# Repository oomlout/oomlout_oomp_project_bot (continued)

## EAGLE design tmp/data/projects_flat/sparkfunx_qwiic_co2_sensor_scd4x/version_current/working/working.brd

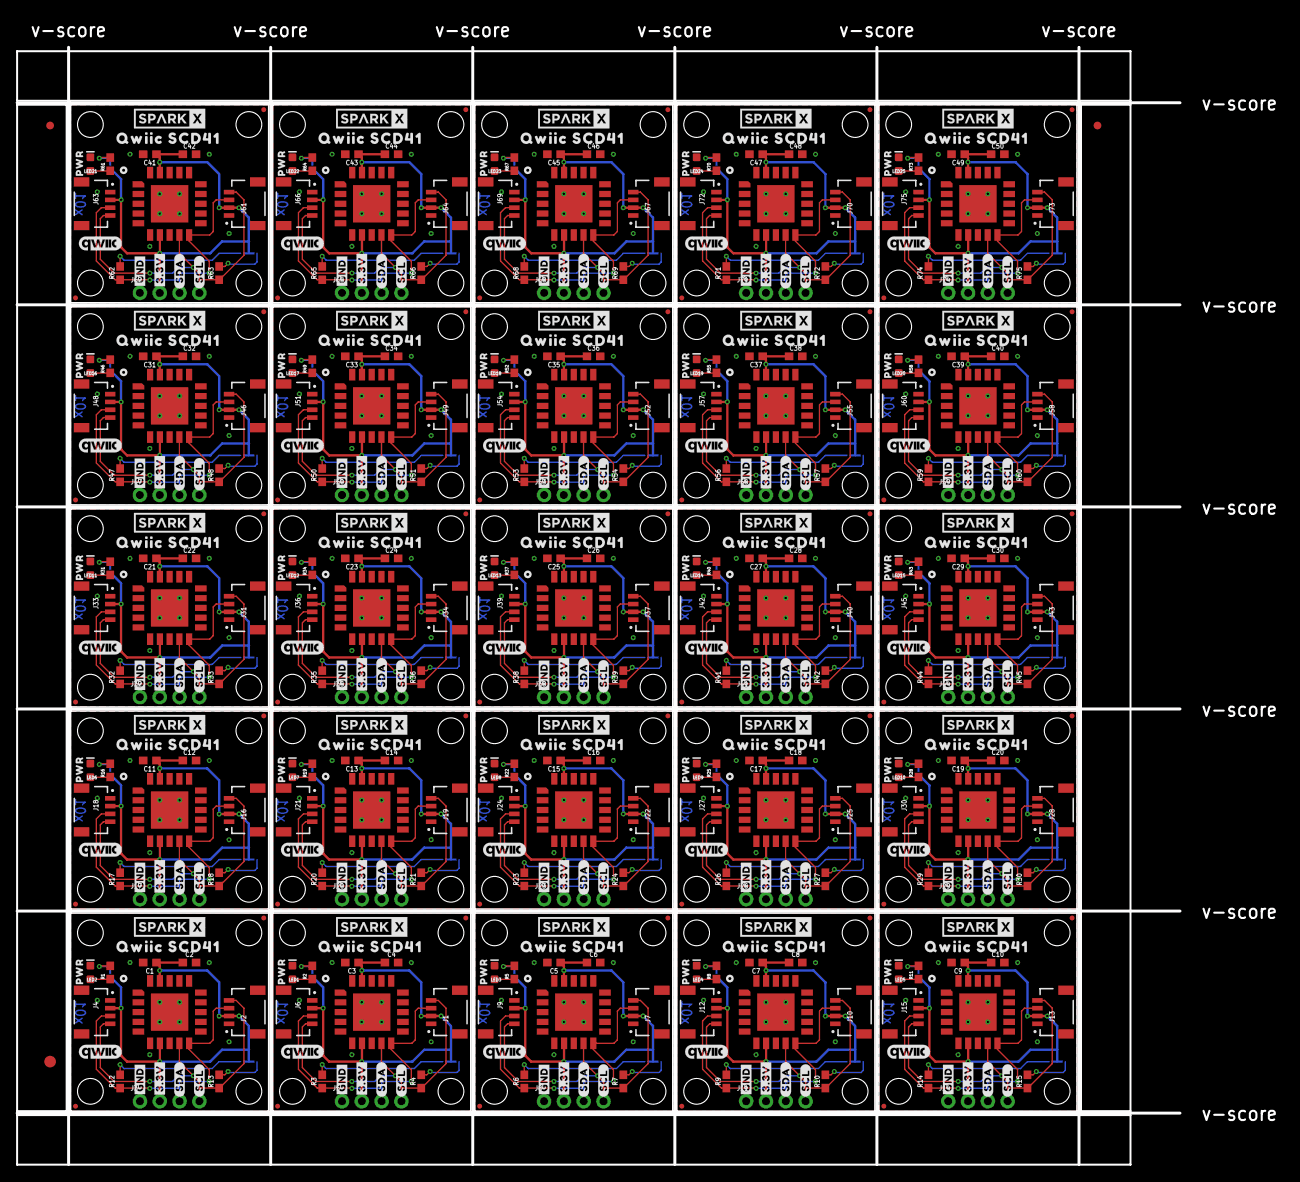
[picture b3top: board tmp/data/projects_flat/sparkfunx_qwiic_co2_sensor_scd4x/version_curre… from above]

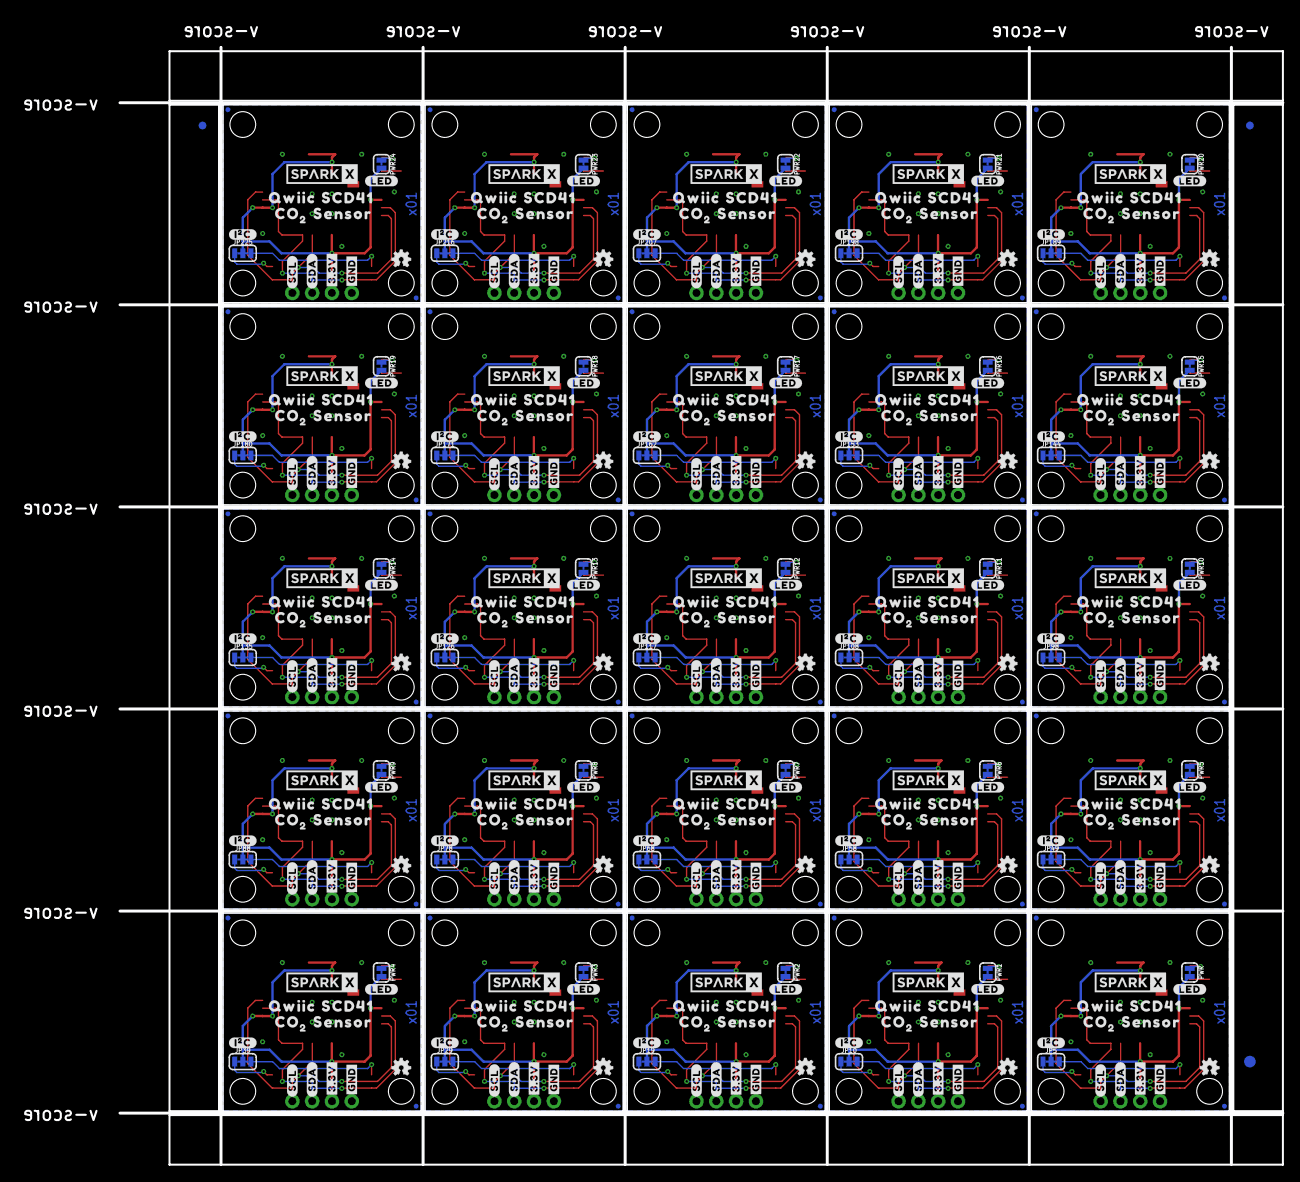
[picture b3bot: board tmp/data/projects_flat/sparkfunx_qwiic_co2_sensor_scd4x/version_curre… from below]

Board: 2 copper layers, 149.1 x 143.3 mm, 1056 parts (428 on the bottom side), 200 nets.

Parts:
C1, C3, C5, C7, C9, C11, C13, C15, C17, C19, C21, C23, C25, C27, C29, C31, C33, C35, C37, C39, C41, C43, C45, C47, C49: 0.1uF; 0603
C2, C4, C6, C8, C10, C12, C14, C16, C18, C20, C22, C24, C26, C28, C30, C32, C34, C36, C38, C40, C42, C44, C46, C48, C50: 4.7uF; 0603
E$1, E$2, E$3, E$4: FIDUCIAL-1X2
E$5, E$6: FIDUCIAL-1.5X3
J1, J2, J4, J6, J7, J9, J10, J12, J13, J15, J16, J18, J19, J21, J22, J24, J25, J27, J28, J30, J31, J33, J34, J36, J37, J39, J40, J42, J43, J45, J46, J48, J49, J51, J52, J54, J55, J57, J58, J60, J61, J63, J64, J66, J67, J69, J70, J72, J73, J75: Qwiic Right Angle; JST04_1MM_RA
J3, J5, J8, J11, J14, J17, J20, J23, J26, J29, J32, J35, J38, J41, J44, J47, J50, J53, J56, J59, J62, J65, J68, J71, J74: PTH; 1X04_NO_SILK
JP1, JP2, JP8, JP9, JP11, JP12, JP17, JP18, JP20, JP22, JP27, JP28, JP30, JP31, JP32, JP37, JP38, JP40, JP41, JP42, JP47, JP48, JP50, JP51, JP56, JP57, JP59, JP60, JP66, JP67, JP69, JP70, JP76, JP77, JP79, JP80, JP86, JP87, JP89, JP90, JP91, JP96, JP97, JP99, JP100, JP101, JP106, JP107, JP109, JP110, JP115, JP116, JP118, JP119, JP124, JP125, JP127, JP128, JP133, JP134, JP136, JP137, JP142, JP143, JP145, JP146, JP151, JP152, JP154, JP155, JP160, JP161, JP163, JP164, JP169, JP170, JP172, JP173, JP178, JP179, JP181, JP182, JP187, JP188, JP190, JP191, JP196, JP197, JP199, JP200, JP205, JP206, JP208, JP209, JP214, JP215, JP217, JP218, JP223, JP224: STAND-OFF
JP3, JP4, JP6, JP7, JP13, JP14, JP15, JP16, JP21, JP23, JP24, JP25, JP26, JP33, JP34, JP35, JP36, JP43, JP44, JP45, JP46, JP52, JP53, JP54, JP55, JP61, JP62, JP63, JP64, JP65, JP71, JP72, JP73, JP74, JP75, JP81, JP82, JP83, JP84, JP85, JP92, JP93, JP94, JP95, JP102, JP103, JP104, JP105, JP111, JP112, JP113, JP114, JP120, JP121, JP122, JP123, JP129, JP130, JP131, JP132, JP138, JP139, JP140, JP141, JP147, JP148, JP149, JP150, JP156, JP157, JP158, JP159, JP165, JP166, JP167, JP168, JP174, JP175, JP176, JP177, JP183, JP184, JP185, JP186, JP192, JP193, JP194, JP195, JP201, JP202, JP203, JP204, JP210, JP211, JP212, JP213, JP219, JP220, JP221, JP222: FIDUCIALUFIDUCIAL; MICRO-FIDUCIAL
JP5, JP10, JP19, JP29, JP39, JP49, JP58, JP68, JP78, JP88, JP98, JP108, JP117, JP126, JP135, JP144, JP153, JP162, JP171, JP180, JP189, JP198, JP207, JP216, JP225: SMT-JUMPER_3_2-NC_TRACE_SILK
LED1, LED2, LED3, LED4, LED5, LED6, LED7, LED8, LED9, LED10, LED11, LED12, LED13, LED14, LED15, LED16, LED17, LED18, LED19, LED20, LED21, LED22, LED23, LED24, LED25: RED; LED-0603
LOGO1, LOGO2, LOGO3, LOGO4, LOGO5, LOGO6, LOGO7, LOGO8, LOGO9, LOGO10, LOGO11, LOGO12, LOGO13, LOGO14, LOGO15, LOGO16, LOGO17, LOGO18, LOGO19, LOGO20, LOGO21, LOGO22, LOGO23, LOGO24, LOGO25: OSHW-LOGOMINI; OSHW-LOGO-MINI
PWR, PWR1, PWR2, PWR3, PWR4, PWR5, PWR6, PWR7, PWR8, PWR9, PWR10, PWR11, PWR12, PWR13, PWR14, PWR15, PWR16, PWR17, PWR18, PWR19, PWR20, PWR21, PWR22, PWR23, PWR24: SMT-JUMPER_2_NC_TRACE_SILK
R1, R2, R5, R8, R11, R16, R19, R22, R25, R28, R31, R34, R37, R40, R43, R46, R49, R52, R55, R58, R61, R64, R67, R70, R73: 1k; 0603
R3, R4, R6, R7, R9, R10, R12, R13, R14, R15, R17, R18, R20, R21, R23, R24, R26, R27, R29, R30, R32, R33, R35, R36, R38, R39, R41, R42, R44, R45, R47, R48, R50, R51, R53, R54, R56, R57, R59, R60, R62, R63, R65, R66, R68, R69, R71, R72, R74, R75: 2.2k; 0603
U1, U2, U3, U4, U5, U6, U7, U8, U9, U10, U11, U12, U13, U14, U15, U16, U17, U18, U19, U20, U21, U22, U23, U24, U25: SCD4X
U$1, U$30, U$57, U$78, U$99, U$120, U$141, U$162, U$183, U$204, U$225, U$246, U$267, U$288, U$309, U$330, U$351, U$372, U$393, U$414, U$435, U$456, U$477, U$498, U$519: CO1
U$2, U$5, U$28, U$38, U$43, U$55, U$64, U$76, U$85, U$97, U$106, U$118, U$127, U$139, U$148, U$160, U$169, U$181, U$190, U$202, U$211, U$223, U$232, U$244, U$253, U$265, U$274, U$286, U$295, U$307, U$316, U$328, U$337, U$349, U$358, U$370, U$379, U$391, U$400, U$412, U$421, U$433, U$442, U$454, U$463, U$475, U$484, U$496, U$505, U$517: SPARKX-LOGO4; SPARKX-MEDIUM
U$3, U$4, U$31, U$32, U$58, U$59, U$79, U$80, U$100, U$101, U$121, U$122, U$142, U$143, U$163, U$164, U$184, U$185, U$205, U$206, U$226, U$227, U$247, U$248, U$268, U$269, U$289, U$290, U$310, U$311, U$331, U$332, U$352, U$353, U$373, U$374, U$394, U$395, U$415, U$416, U$436, U$437, U$457, U$458, U$478, U$479, U$499, U$500, U$520, U$521: QWIIC0
U$6, U$11, U$19, U$34, U$44, U$47, U$65, U$68, U$86, U$89, U$107, U$110, U$128, U$131, U$149, U$152, U$170, U$173, U$191, U$194, U$212, U$215, U$233, U$236, U$254, U$257, U$275, U$278, U$296, U$299, U$317, U$320, U$338, U$341, U$359, U$362, U$380, U$383, U$401, U$404, U$422, U$425, U$443, U$446, U$464, U$467, U$485, U$488, U$506, U$509: #3#3V#0
U$7, U$17, U$20, U$35, U$45, U$48, U$66, U$69, U$87, U$90, U$108, U$111, U$129, U$132, U$150, U$153, U$171, U$174, U$192, U$195, U$213, U$216, U$234, U$237, U$255, U$258, U$276, U$279, U$297, U$300, U$318, U$321, U$339, U$342, U$360, U$363, U$381, U$384, U$402, U$405, U$423, U$426, U$444, U$447, U$465, U$468, U$486, U$489, U$507, U$510: #SDA#0
U$8, U$18, U$21, U$36, U$46, U$49, U$67, U$70, U$88, U$91, U$109, U$112, U$130, U$133, U$151, U$154, U$172, U$175, U$193, U$196, U$214, U$217, U$235, U$238, U$256, U$259, U$277, U$280, U$298, U$301, U$319, U$322, U$340, U$343, U$361, U$364, U$382, U$385, U$403, U$406, U$424, U$427, U$445, U$448, U$466, U$469, U$487, U$490, U$508, U$511: #SCL#0
U$9, U$22, U$24, U$33, U$50, U$51, U$71, U$72, U$92, U$93, U$113, U$114, U$134, U$135, U$155, U$156, U$176, U$177, U$197, U$198, U$218, U$219, U$239, U$240, U$260, U$261, U$281, U$282, U$302, U$303, U$323, U$324, U$344, U$345, U$365, U$366, U$386, U$387, U$407, U$408, U$428, U$429, U$449, U$450, U$470, U$471, U$491, U$492, U$512, U$513: #GND#0
U$10, U$25, U$52, U$73, U$94, U$115, U$136, U$157, U$178, U$199, U$220, U$241, U$262, U$283, U$304, U$325, U$346, U$367, U$388, U$409, U$430, U$451, U$472, U$493, U$514: #I�C#1
U$12, U$26, U$53, U$74, U$95, U$116, U$137, U$158, U$179, U$200, U$221, U$242, U$263, U$284, U$305, U$326, U$347, U$368, U$389, U$410, U$431, U$452, U$473, U$494, U$515: PWR0
U$13, U$37, U$60, U$81, U$102, U$123, U$144, U$165, U$186, U$207, U$228, U$249, U$270, U$291, U$312, U$333, U$354, U$375, U$396, U$417, U$438, U$459, U$480, U$501, U$522: SENSOR3
U$14, U$39, U$61, U$82, U$103, U$124, U$145, U$166, U$187, U$208, U$229, U$250, U$271, U$292, U$313, U$334, U$355, U$376, U$397, U$418, U$439, U$460, U$481, U$502, U$523: 20
U$15, U$16, U$40, U$41, U$62, U$63, U$83, U$84, U$104, U$105, U$125, U$126, U$146, U$147, U$167, U$168, U$188, U$189, U$209, U$210, U$230, U$231, U$251, U$252, U$272, U$273, U$293, U$294, U$314, U$315, U$335, U$336, U$356, U$357, U$377, U$378, U$398, U$399, U$419, U$420, U$440, U$441, U$461, U$462, U$482, U$483, U$503, U$504, U$524, U$525: SCD410
U$23, U$27, U$54, U$75, U$96, U$117, U$138, U$159, U$180, U$201, U$222, U$243, U$264, U$285, U$306, U$327, U$348, U$369, U$390, U$411, U$432, U$453, U$474, U$495, U$516: #LED#0
U$29, U$42, U$56, U$77, U$98, U$119, U$140, U$161, U$182, U$203, U$224, U$245, U$266, U$287, U$308, U$329, U$350, U$371, U$392, U$413, U$434, U$455, U$476, U$497, U$518: QWIIC_5.5MM

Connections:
3.3V: C1.1, C2.1, J2.2, J3.2, J4.2, JP5.2, PWR.2, U3.7, U3.19
3.3V1: C3.1, C4.1, J1.2, J5.2, J6.2, JP10.2, PWR1.2, U1.7, U1.19
3.3V2: C5.1, C6.1, J7.2, J8.2, J9.2, JP19.2, PWR2.2, U2.7, U2.19
3.3V3: C7.1, C8.1, J10.2, J11.2, J12.2, JP29.2, PWR3.2, U4.7, U4.19
3.3V4: C9.1, C10.1, J13.2, J14.2, J15.2, JP39.2, PWR4.2, U5.7, U5.19
3.3V5: C11.1, C12.1, J16.2, J17.2, J18.2, JP49.2, PWR5.2, U6.7, U6.19
3.3V6: C13.1, C14.1, J19.2, J20.2, J21.2, JP58.2, PWR6.2, U7.7, U7.19
3.3V7: C15.1, C16.1, J22.2, J23.2, J24.2, JP68.2, PWR7.2, U8.7, U8.19
3.3V8: C17.1, C18.1, J25.2, J26.2, J27.2, JP78.2, PWR8.2, U9.7, U9.19
3.3V9: C19.1, C20.1, J28.2, J29.2, J30.2, JP88.2, PWR9.2, U10.7, U10.19
3.3V10: C21.1, C22.1, J31.2, J32.2, J33.2, JP98.2, PWR10.2, U11.7, U11.19
3.3V11: C23.1, C24.1, J34.2, J35.2, J36.2, JP108.2, PWR11.2, U12.7, U12.19
3.3V12: C25.1, C26.1, J37.2, J38.2, J39.2, JP117.2, PWR12.2, U13.7, U13.19
3.3V13: C27.1, C28.1, J40.2, J41.2, J42.2, JP126.2, PWR13.2, U14.7, U14.19
3.3V14: C29.1, C30.1, J43.2, J44.2, J45.2, JP135.2, PWR14.2, U15.7, U15.19
3.3V15: C31.1, C32.1, J46.2, J47.2, J48.2, JP144.2, PWR15.2, U16.7, U16.19
3.3V16: C33.1, C34.1, J49.2, J50.2, J51.2, JP153.2, PWR16.2, U17.7, U17.19
3.3V17: C35.1, C36.1, J52.2, J53.2, J54.2, JP162.2, PWR17.2, U18.7, U18.19
3.3V18: C37.1, C38.1, J55.2, J56.2, J57.2, JP171.2, PWR18.2, U19.7, U19.19
3.3V19: C39.1, C40.1, J58.2, J59.2, J60.2, JP180.2, PWR19.2, U20.7, U20.19
3.3V20: C41.1, C42.1, J61.2, J62.2, J63.2, JP189.2, PWR20.2, U21.7, U21.19
3.3V21: C43.1, C44.1, J64.2, J65.2, J66.2, JP198.2, PWR21.2, U22.7, U22.19
3.3V22: C45.1, C46.1, J67.2, J68.2, J69.2, JP207.2, PWR22.2, U23.7, U23.19
3.3V23: C47.1, C48.1, J70.2, J71.2, J72.2, JP216.2, PWR23.2, U24.7, U24.19
3.3V24: C49.1, C50.1, J73.2, J74.2, J75.2, JP225.2, PWR24.2, U25.7, U25.19
GND: C1.2, C2.2, J2.1, J3.1, J4.1, LED2.C, U3.6, U3.20, U3.CP
GND1: C3.2, C4.2, J1.1, J5.1, J6.1, LED1.C, U1.6, U1.20, U1.CP
GND2: C5.2, C6.2, J7.1, J8.1, J9.1, LED3.C, U2.6, U2.20, U2.CP
GND3: C7.2, C8.2, J10.1, J11.1, J12.1, LED4.C, U4.6, U4.20, U4.CP
GND4: C9.2, C10.2, J13.1, J14.1, J15.1, LED5.C, U5.6, U5.20, U5.CP
GND5: C11.2, C12.2, J16.1, J17.1, J18.1, LED6.C, U6.6, U6.20, U6.CP
GND6: C13.2, C14.2, J19.1, J20.1, J21.1, LED7.C, U7.6, U7.20, U7.CP
GND7: C15.2, C16.2, J22.1, J23.1, J24.1, LED8.C, U8.6, U8.20, U8.CP
GND8: C17.2, C18.2, J25.1, J26.1, J27.1, LED9.C, U9.6, U9.20, U9.CP
GND9: C19.2, C20.2, J28.1, J29.1, J30.1, LED10.C, U10.6, U10.20, U10.CP
GND10: C21.2, C22.2, J31.1, J32.1, J33.1, LED11.C, U11.6, U11.20, U11.CP
GND11: C23.2, C24.2, J34.1, J35.1, J36.1, LED12.C, U12.6, U12.20, U12.CP
GND12: C25.2, C26.2, J37.1, J38.1, J39.1, LED13.C, U13.6, U13.20, U13.CP
GND13: C27.2, C28.2, J40.1, J41.1, J42.1, LED14.C, U14.6, U14.20, U14.CP
GND14: C29.2, C30.2, J43.1, J44.1, J45.1, LED15.C, U15.6, U15.20, U15.CP
GND15: C31.2, C32.2, J46.1, J47.1, J48.1, LED16.C, U16.6, U16.20, U16.CP
GND16: C33.2, C34.2, J49.1, J50.1, J51.1, LED17.C, U17.6, U17.20, U17.CP
GND17: C35.2, C36.2, J52.1, J53.1, J54.1, LED18.C, U18.6, U18.20, U18.CP
GND18: C37.2, C38.2, J55.1, J56.1, J57.1, LED19.C, U19.6, U19.20, U19.CP
GND19: C39.2, C40.2, J58.1, J59.1, J60.1, LED20.C, U20.6, U20.20, U20.CP
GND20: C41.2, C42.2, J61.1, J62.1, J63.1, LED21.C, U21.6, U21.20, U21.CP
GND21: C43.2, C44.2, J64.1, J65.1, J66.1, LED22.C, U22.6, U22.20, U22.CP
GND22: C45.2, C46.2, J67.1, J68.1, J69.1, LED23.C, U23.6, U23.20, U23.CP
GND23: C47.2, C48.2, J70.1, J71.1, J72.1, LED24.C, U24.6, U24.20, U24.CP
GND24: C49.2, C50.2, J73.1, J74.1, J75.1, LED25.C, U25.6, U25.20, U25.CP
unnamed: LED1.A, R2.1
unnamed: PWR1.1, R2.2
unnamed: JP10.1, R4.2
unnamed: JP10.3, R3.2
unnamed: LED3.A, R5.1
unnamed: PWR2.1, R5.2
unnamed: JP19.1, R7.2
unnamed: JP19.3, R6.2
unnamed: JP5.1, R13.2
unnamed: LED2.A, R1.1
unnamed: LED4.A, R8.1
unnamed: PWR3.1, R8.2
unnamed: JP29.1, R10.2
unnamed: JP29.3, R9.2
unnamed: JP5.3, R12.2
unnamed: LED5.A, R11.1
unnamed: PWR.1, R1.2
unnamed: PWR4.1, R11.2
unnamed: JP39.1, R15.2
unnamed: JP39.3, R14.2
unnamed: LED6.A, R16.1
unnamed: PWR5.1, R16.2
unnamed: JP49.1, R18.2
unnamed: JP49.3, R17.2
unnamed: LED7.A, R19.1
unnamed: PWR6.1, R19.2
unnamed: JP58.1, R21.2
unnamed: JP58.3, R20.2
unnamed: LED8.A, R22.1
unnamed: PWR7.1, R22.2
unnamed: JP68.1, R24.2
unnamed: JP68.3, R23.2
unnamed: LED9.A, R25.1
unnamed: PWR8.1, R25.2
unnamed: JP78.1, R27.2
unnamed: JP78.3, R26.2
unnamed: LED10.A, R28.1
unnamed: PWR9.1, R28.2
unnamed: JP88.1, R30.2
unnamed: JP88.3, R29.2
unnamed: LED11.A, R31.1
unnamed: PWR10.1, R31.2
unnamed: JP98.1, R33.2
unnamed: JP98.3, R32.2
unnamed: LED12.A, R34.1
unnamed: PWR11.1, R34.2
unnamed: JP108.1, R36.2
unnamed: JP108.3, R35.2
unnamed: LED13.A, R37.1
unnamed: PWR12.1, R37.2
unnamed: JP117.1, R39.2
unnamed: JP117.3, R38.2
unnamed: LED14.A, R40.1
unnamed: PWR13.1, R40.2
unnamed: JP126.1, R42.2
unnamed: JP126.3, R41.2
unnamed: LED15.A, R43.1
unnamed: PWR14.1, R43.2
unnamed: JP135.1, R45.2
unnamed: JP135.3, R44.2
unnamed: LED16.A, R46.1
unnamed: PWR15.1, R46.2
unnamed: JP144.1, R48.2
unnamed: JP144.3, R47.2
unnamed: LED17.A, R49.1
unnamed: PWR16.1, R49.2
unnamed: JP153.1, R51.2
unnamed: JP153.3, R50.2
unnamed: LED18.A, R52.1
unnamed: PWR17.1, R52.2
unnamed: JP162.1, R54.2
unnamed: JP162.3, R53.2
unnamed: LED19.A, R55.1
unnamed: PWR18.1, R55.2
unnamed: JP171.1, R57.2
unnamed: JP171.3, R56.2
unnamed: LED20.A, R58.1
unnamed: PWR19.1, R58.2
unnamed: JP180.1, R60.2
unnamed: JP180.3, R59.2
unnamed: LED21.A, R61.1
unnamed: PWR20.1, R61.2
unnamed: JP189.1, R63.2
unnamed: JP189.3, R62.2
unnamed: LED22.A, R64.1
unnamed: PWR21.1, R64.2
unnamed: JP198.1, R66.2
unnamed: JP198.3, R65.2
unnamed: LED23.A, R67.1
unnamed: PWR22.1, R67.2
unnamed: JP207.1, R69.2
unnamed: JP207.3, R68.2
unnamed: LED24.A, R70.1
unnamed: PWR23.1, R70.2
unnamed: JP216.1, R72.2
unnamed: JP216.3, R71.2
unnamed: LED25.A, R73.1
unnamed: PWR24.1, R73.2
unnamed: JP225.1, R75.2
unnamed: JP225.3, R74.2
SCL: J2.4, J3.4, J4.4, R13.1, U3.9
SCL1: J1.4, J5.4, J6.4, R4.1, U1.9
SCL2: J7.4, J8.4, J9.4, R7.1, U2.9
SCL3: J10.4, J11.4, J12.4, R10.1, U4.9
SCL4: J13.4, J14.4, J15.4, R15.1, U5.9
SCL5: J16.4, J17.4, J18.4, R18.1, U6.9
SCL6: J19.4, J20.4, J21.4, R21.1, U7.9
SCL7: J22.4, J23.4, J24.4, R24.1, U8.9
SCL8: J25.4, J26.4, J27.4, R27.1, U9.9
SCL9: J28.4, J29.4, J30.4, R30.1, U10.9
SCL10: J31.4, J32.4, J33.4, R33.1, U11.9
SCL11: J34.4, J35.4, J36.4, R36.1, U12.9
SCL12: J37.4, J38.4, J39.4, R39.1, U13.9
SCL13: J40.4, J41.4, J42.4, R42.1, U14.9
SCL14: J43.4, J44.4, J45.4, R45.1, U15.9
SCL15: J46.4, J47.4, J48.4, R48.1, U16.9
SCL16: J49.4, J50.4, J51.4, R51.1, U17.9
SCL17: J52.4, J53.4, J54.4, R54.1, U18.9
SCL18: J55.4, J56.4, J57.4, R57.1, U19.9
SCL19: J58.4, J59.4, J60.4, R60.1, U20.9
SCL20: J61.4, J62.4, J63.4, R63.1, U21.9
SCL21: J64.4, J65.4, J66.4, R66.1, U22.9
SCL22: J67.4, J68.4, J69.4, R69.1, U23.9
SCL23: J70.4, J71.4, J72.4, R72.1, U24.9
SCL24: J73.4, J74.4, J75.4, R75.1, U25.9
SDA: J2.3, J3.3, J4.3, R12.1, U3.10
SDA1: J1.3, J5.3, J6.3, R3.1, U1.10
SDA2: J7.3, J8.3, J9.3, R6.1, U2.10
SDA3: J10.3, J11.3, J12.3, R9.1, U4.10
SDA4: J13.3, J14.3, J15.3, R14.1, U5.10
SDA5: J16.3, J17.3, J18.3, R17.1, U6.10
SDA6: J19.3, J20.3, J21.3, R20.1, U7.10
SDA7: J22.3, J23.3, J24.3, R23.1, U8.10
SDA8: J25.3, J26.3, J27.3, R26.1, U9.10
SDA9: J28.3, J29.3, J30.3, R29.1, U10.10
SDA10: J31.3, J32.3, J33.3, R32.1, U11.10
SDA11: J34.3, J35.3, J36.3, R35.1, U12.10
SDA12: J37.3, J38.3, J39.3, R38.1, U13.10
SDA13: J40.3, J41.3, J42.3, R41.1, U14.10
SDA14: J43.3, J44.3, J45.3, R44.1, U15.10
SDA15: J46.3, J47.3, J48.3, R47.1, U16.10
SDA16: J49.3, J50.3, J51.3, R50.1, U17.10
SDA17: J52.3, J53.3, J54.3, R53.1, U18.10
SDA18: J55.3, J56.3, J57.3, R56.1, U19.10
SDA19: J58.3, J59.3, J60.3, R59.1, U20.10
SDA20: J61.3, J62.3, J63.3, R62.1, U21.10
SDA21: J64.3, J65.3, J66.3, R65.1, U22.10
SDA22: J67.3, J68.3, J69.3, R68.1, U23.10
SDA23: J70.3, J71.3, J72.3, R71.1, U24.10
SDA24: J73.3, J74.3, J75.3, R74.1, U25.10

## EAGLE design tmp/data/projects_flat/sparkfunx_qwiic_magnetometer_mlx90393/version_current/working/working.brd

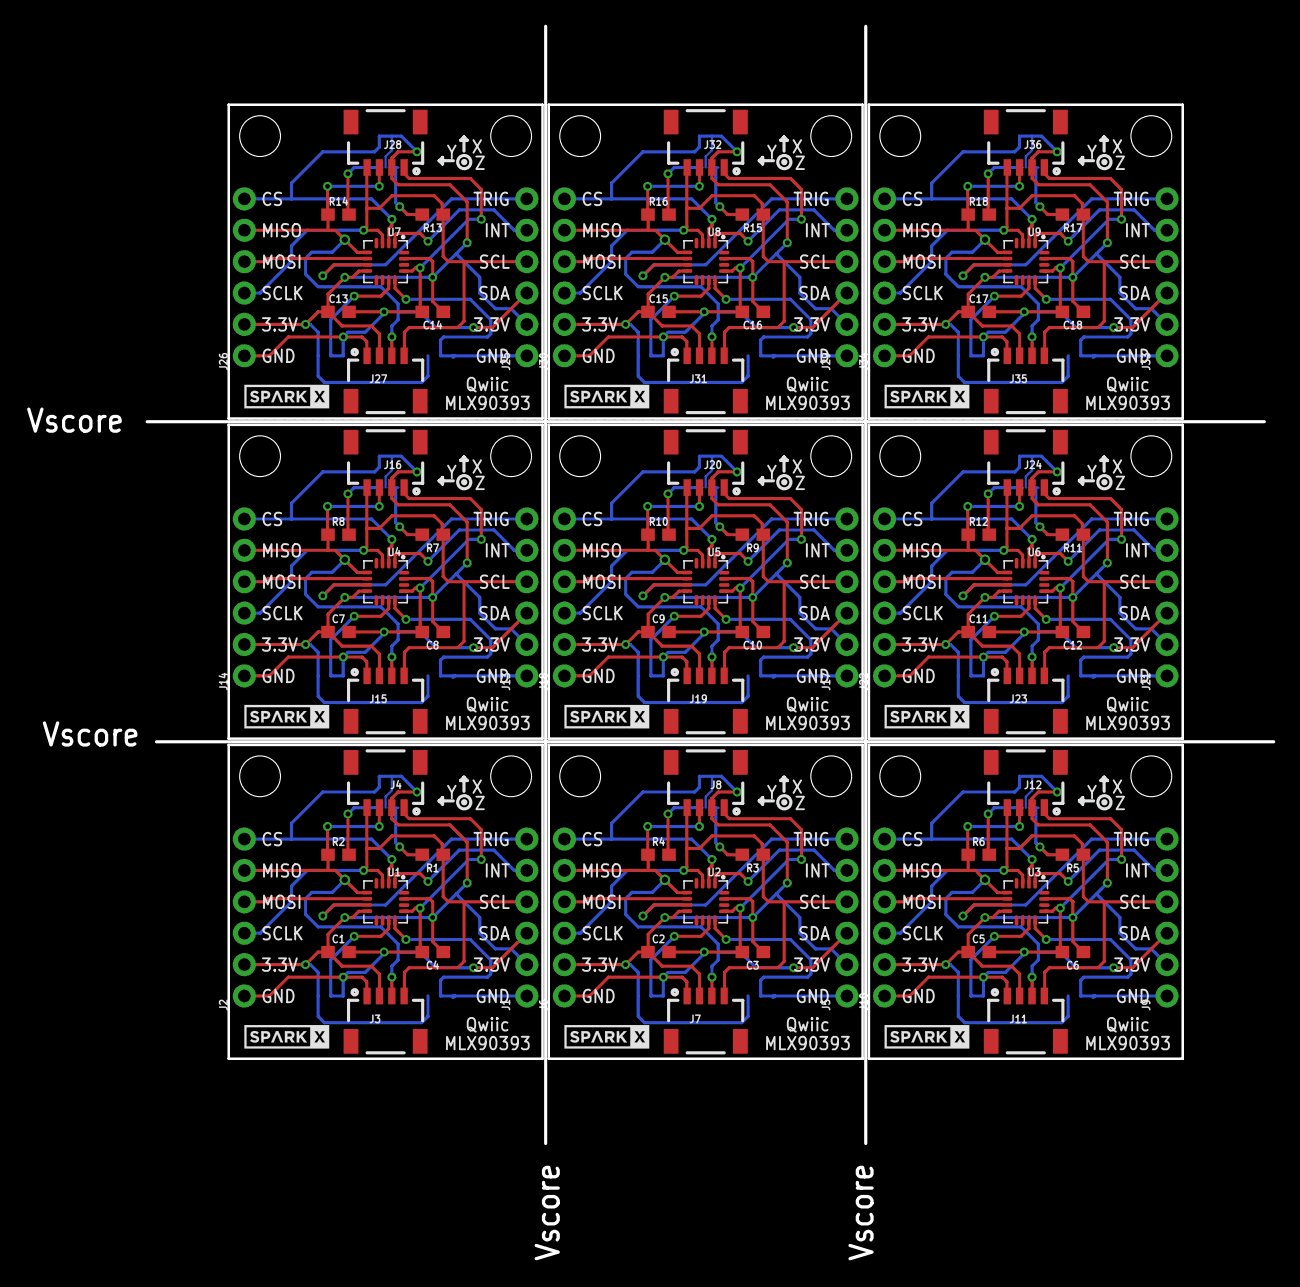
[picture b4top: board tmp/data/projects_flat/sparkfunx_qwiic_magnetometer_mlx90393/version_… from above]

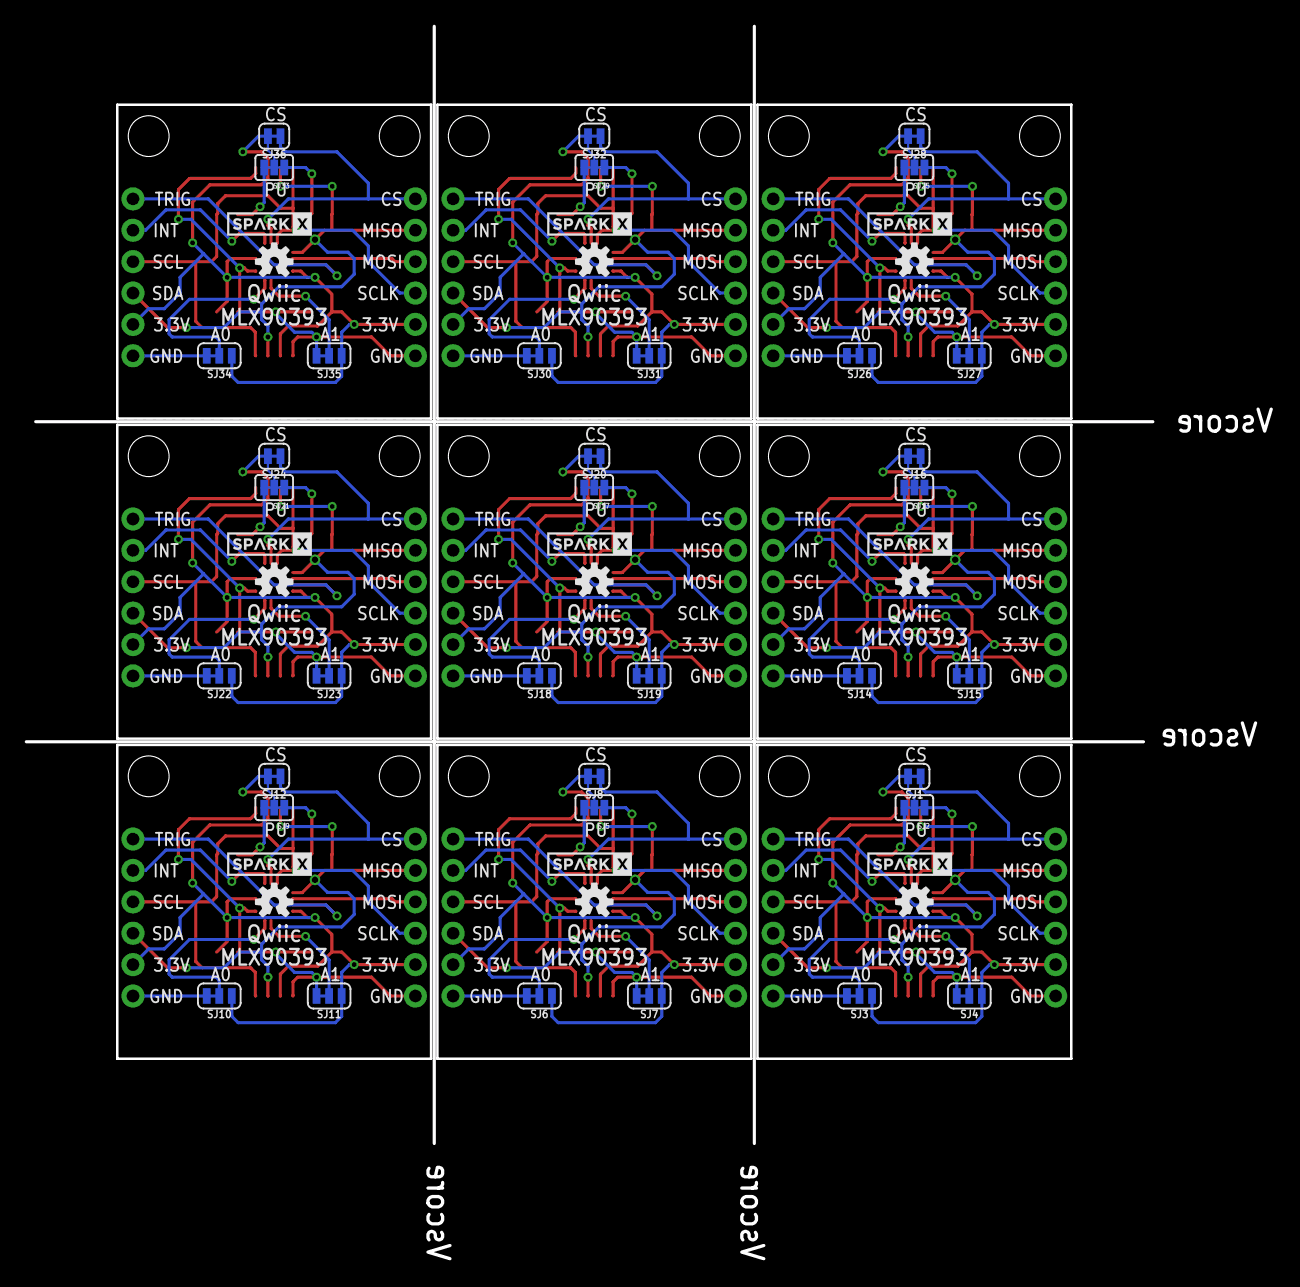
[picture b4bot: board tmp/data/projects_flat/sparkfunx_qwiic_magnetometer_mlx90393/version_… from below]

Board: 2 copper layers, 91.2 x 90.4 mm, 163 parts (54 on the bottom side), 108 nets.

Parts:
C1, C2, C3, C4, C5, C6, C7, C8, C9, C10, C11, C12, C13, C14, C15, C16, C17, C18: 0.1uF; 0603
FRAME2: FRAME-LETTER; CREATIVE_COMMONS
J1, J2, J5, J6, J9, J10, J13, J14, J17, J18, J21, J22, J25, J26, J29, J30, J33, J34: 1X06_NO_SILK
J3, J4, J7, J8, J11, J12, J15, J16, J19, J20, J23, J24, J27, J28, J31, J32, J35, J36: 1X04_1MM_RA
JP1, JP2, JP3, JP4, JP5, JP6, JP7, JP8, JP9, JP10, JP11, JP12, JP13, JP14, JP15, JP16, JP17, JP18: STAND-OFF
R1, R2, R3, R4, R5, R6, R7, R8, R9, R10, R11, R12, R13, R14, R15, R16, R17, R18: 10k; 0603
SJ1, SJ8, SJ12, SJ16, SJ20, SJ24, SJ28, SJ32, SJ36: SMT-JUMPER_2_NC_TRACE_SILK
SJ2, SJ5, SJ9, SJ13, SJ17, SJ21, SJ25, SJ29, SJ33: PAD-JUMPER-3-3OF3_NC_BY_TRACE_YES_SILK_FULL_BOX
SJ3, SJ4, SJ6, SJ7, SJ10, SJ11, SJ14, SJ15, SJ18, SJ19, SJ22, SJ23, SJ26, SJ27, SJ30, SJ31, SJ34, SJ35: SMT-JUMPER_3_1-NC_TRACE_SILK
U1, U2, U3, U4, U5, U6, U7, U8, U9: MLX90393_MAGNETOMETER; QFN-16
U$1, U$4, U$7, U$10, U$13, U$16, U$19, U$22, U$25: OSHW-LOGOS; OSHW-LOGO-S
U$2, U$3, U$5, U$6, U$8, U$9, U$11, U$12, U$14, U$15, U$17, U$18, U$20, U$21, U$23, U$24, U$26, U$27: SPARKX-LOGO3; SPARKX-SMALL

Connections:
3.3V: C1.1, C4.1, J1.2, J2.2, J3.2, J4.2, SJ1.2, SJ2.2, SJ3.1, SJ4.1, U1.8, U1.15
3.3V1: C2.1, C3.1, J5.2, J6.2, J7.2, J8.2, SJ5.2, SJ6.1, SJ7.1, SJ8.2, U2.8, U2.15
3.3V2: C5.1, C6.1, J9.2, J10.2, J11.2, J12.2, SJ9.2, SJ10.1, SJ11.1, SJ12.2, U3.8, U3.15
3.3V3: C7.1, C8.1, J13.2, J14.2, J15.2, J16.2, SJ13.2, SJ14.1, SJ15.1, SJ16.2, U4.8, U4.15
3.3V4: C9.1, C10.1, J17.2, J18.2, J19.2, J20.2, SJ17.2, SJ18.1, SJ19.1, SJ20.2, U5.8, U5.15
3.3V5: C11.1, C12.1, J21.2, J22.2, J23.2, J24.2, SJ21.2, SJ22.1, SJ23.1, SJ24.2, U6.8, U6.15
3.3V6: C13.1, C14.1, J25.2, J26.2, J27.2, J28.2, SJ25.2, SJ26.1, SJ27.1, SJ28.2, U7.8, U7.15
3.3V7: C15.1, C16.1, J29.2, J30.2, J31.2, J32.2, SJ29.2, SJ30.1, SJ31.1, SJ32.2, U8.8, U8.15
3.3V8: C17.1, C18.1, J33.2, J34.2, J35.2, J36.2, SJ33.2, SJ34.1, SJ35.1, SJ36.2, U9.8, U9.15
A0: SJ3.2, U1.12
A1: SJ4.2, U1.11
A2: SJ6.2, U2.12
A3: SJ7.2, U2.11
A4: SJ10.2, U3.12
A5: SJ11.2, U3.11
A6: SJ14.2, U4.12
A7: SJ15.2, U4.11
A8: SJ18.2, U5.12
A9: SJ19.2, U5.11
A10: SJ22.2, U6.12
A11: SJ23.2, U6.11
A12: SJ26.2, U7.12
A13: SJ27.2, U7.11
A14: SJ30.2, U8.12
A15: SJ31.2, U8.11
A16: SJ34.2, U9.12
A17: SJ35.2, U9.11
CS: J2.6, SJ1.1, U1.2
CS1: J6.6, SJ8.1, U2.2
CS2: J10.6, SJ12.1, U3.2
CS3: J14.6, SJ16.1, U4.2
CS4: J18.6, SJ20.1, U5.2
CS5: J22.6, SJ24.1, U6.2
CS6: J26.6, SJ28.1, U7.2
CS7: J30.6, SJ32.1, U8.2
CS8: J34.6, SJ36.1, U9.2
GND: C1.2, C4.2, J1.1, J2.1, J3.1, J4.1, SJ3.3, SJ4.3, U1.13
GND1: C2.2, C3.2, J5.1, J6.1, J7.1, J8.1, SJ6.3, SJ7.3, U2.13
GND2: C5.2, C6.2, J9.1, J10.1, J11.1, J12.1, SJ10.3, SJ11.3, U3.13
GND3: C7.2, C8.2, J13.1, J14.1, J15.1, J16.1, SJ14.3, SJ15.3, U4.13
GND4: C9.2, C10.2, J17.1, J18.1, J19.1, J20.1, SJ18.3, SJ19.3, U5.13
GND5: C11.2, C12.2, J21.1, J22.1, J23.1, J24.1, SJ22.3, SJ23.3, U6.13
GND6: C13.2, C14.2, J25.1, J26.1, J27.1, J28.1, SJ26.3, SJ27.3, U7.13
GND7: C15.2, C16.2, J29.1, J30.1, J31.1, J32.1, SJ30.3, SJ31.3, U8.13
GND8: C17.2, C18.2, J33.1, J34.1, J35.1, J36.1, SJ34.3, SJ35.3, U9.13
INT: J1.5, U1.1
INT1: J5.5, U2.1
INT2: J9.5, U3.1
INT3: J13.5, U4.1
INT4: J17.5, U5.1
INT5: J21.5, U6.1
INT6: J25.5, U7.1
INT7: J29.5, U8.1
INT8: J33.5, U9.1
MISO: J2.4, U1.6
MISO1: J6.4, U2.6
MISO2: J10.4, U3.6
MISO3: J14.4, U4.6
MISO4: J18.4, U5.6
MISO5: J22.4, U6.6
MISO6: J26.4, U7.6
MISO7: J30.4, U8.6
MISO8: J34.4, U9.6
unnamed: R4.2, SJ5.1
unnamed: R3.2, SJ5.3
unnamed: R6.2, SJ9.1
unnamed: R2.2, SJ2.1
unnamed: R1.2, SJ2.3
unnamed: R5.2, SJ9.3
unnamed: R8.2, SJ13.1
unnamed: R7.2, SJ13.3
unnamed: R10.2, SJ17.1
unnamed: R9.2, SJ17.3
unnamed: R12.2, SJ21.1
unnamed: R11.2, SJ21.3
unnamed: R14.2, SJ25.1
unnamed: R13.2, SJ25.3
unnamed: R16.2, SJ29.1
unnamed: R15.2, SJ29.3
unnamed: R18.2, SJ33.1
unnamed: R17.2, SJ33.3
SCL: J1.4, J2.3, J3.4, J4.4, R1.1, U1.3
SCL1: J5.4, J6.3, J7.4, J8.4, R3.1, U2.3
SCL2: J9.4, J10.3, J11.4, J12.4, R5.1, U3.3
SCL3: J13.4, J14.3, J15.4, J16.4, R7.1, U4.3
SCL4: J17.4, J18.3, J19.4, J20.4, R9.1, U5.3
SCL5: J21.4, J22.3, J23.4, J24.4, R11.1, U6.3
SCL6: J25.4, J26.3, J27.4, J28.4, R13.1, U7.3
SCL7: J29.4, J30.3, J31.4, J32.4, R15.1, U8.3
SCL8: J33.4, J34.3, J35.4, J36.4, R17.1, U9.3
SDA: J1.3, J2.5, J3.3, J4.3, R2.1, U1.5
SDA1: J5.3, J6.5, J7.3, J8.3, R4.1, U2.5
SDA2: J9.3, J10.5, J11.3, J12.3, R6.1, U3.5
SDA3: J13.3, J14.5, J15.3, J16.3, R8.1, U4.5
SDA4: J17.3, J18.5, J19.3, J20.3, R10.1, U5.5
SDA5: J21.3, J22.5, J23.3, J24.3, R12.1, U6.5
SDA6: J25.3, J26.5, J27.3, J28.3, R14.1, U7.5
SDA7: J29.3, J30.5, J31.3, J32.3, R16.1, U8.5
SDA8: J33.3, J34.5, J35.3, J36.3, R18.1, U9.5
TRIG: J1.6, U1.7
TRIG1: J5.6, U2.7
TRIG2: J9.6, U3.7
TRIG3: J13.6, U4.7
TRIG4: J17.6, U5.7
TRIG5: J21.6, U6.7
TRIG6: J25.6, U7.7
TRIG7: J29.6, U8.7
TRIG8: J33.6, U9.7

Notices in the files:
parts and their libraries:
SparkFun-Resistors: Licensing: Creative Commons ShareAlike 4.0 International - https://creativecommons.org/licenses/by-sa/4.0
SparkFun-Aesthetics: Released under the Creative Commons Attribution Share-Alike 4.0 License
SparkFun-Aesthetics: https://creativecommons.org/licenses/by-sa/4.0
